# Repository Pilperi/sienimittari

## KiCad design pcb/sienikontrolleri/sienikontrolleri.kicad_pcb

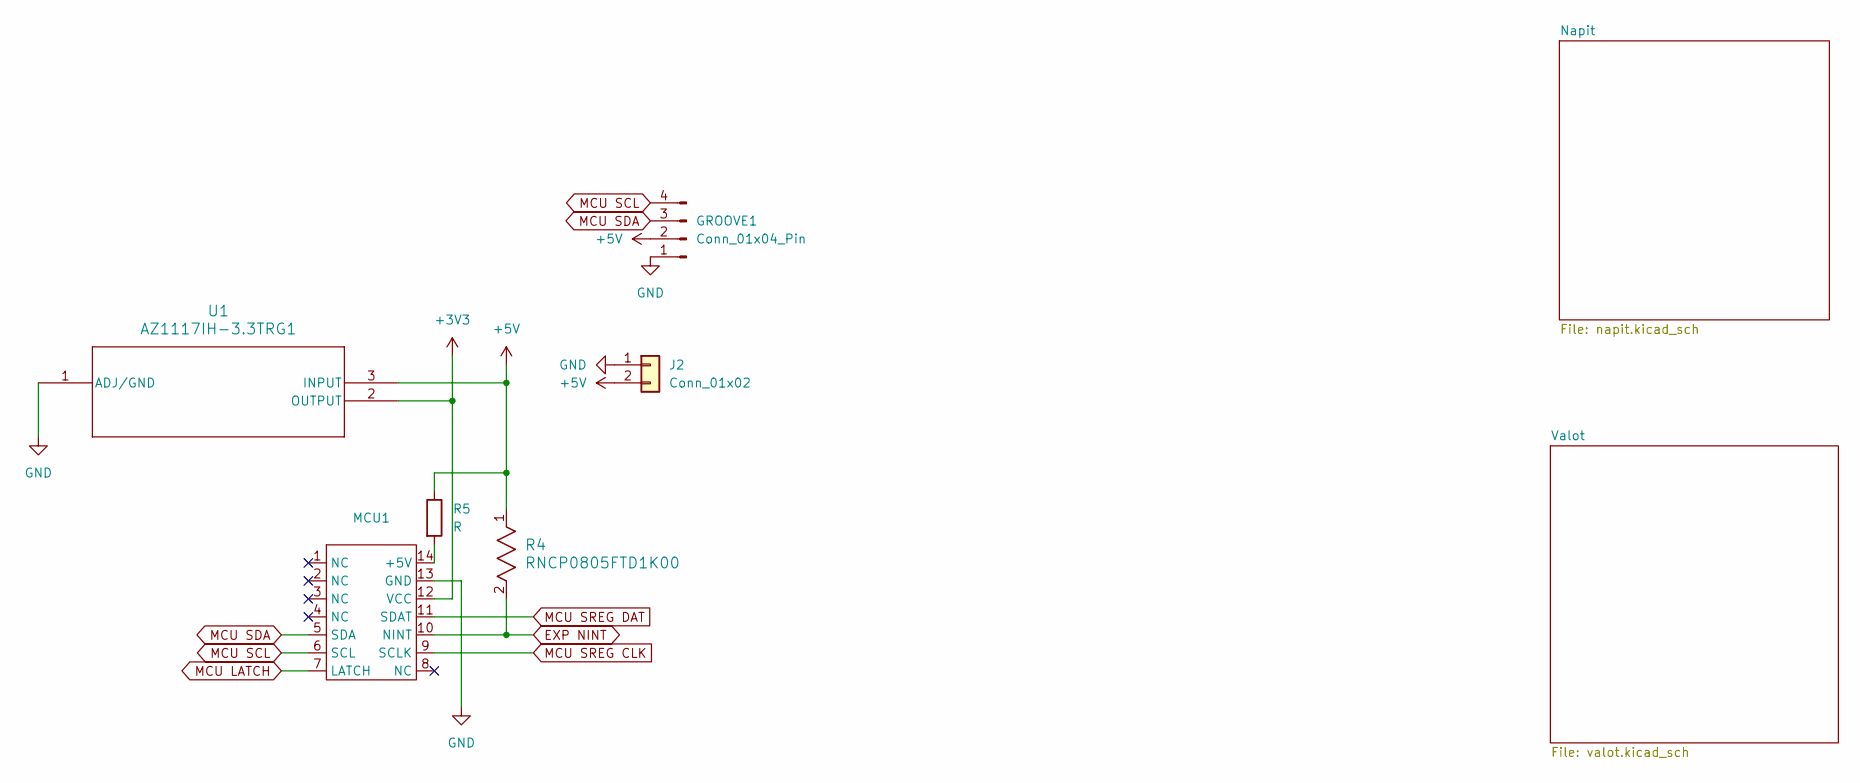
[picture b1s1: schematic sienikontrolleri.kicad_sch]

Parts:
GROOVE1: Conn_01x04_Pin; PinHeader_1x04_P2.00mm_Vertical
J2: Conn_01x02; PinHeader_1x02_P2.54mm_Vertical
MCU1: MCU 14
R4: RNCP0805FTD1K00; STA_RNCP0805_STP
R5: R; R_0805_2012Metric_Pad1.20x1.40mm_HandSolder
U1: AZ1117IH-3.3TRG1; SOT223_AZ1117I_6P5X3P5_DIO

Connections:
+3V3: MCU1.12 (VCC), U1.2 (OUTPUT)
+5V: GROOVE1.2, J2.2, R4.1, R5.1, U1.3 (INPUT); also elsewhere on the board
EXP NINT: MCU1.10 (NINT), R4.2; also elsewhere on the board
GND: GROOVE1.1, J2.1, MCU1.13 (GND), U1.1 (ADJ/GND); also elsewhere on the board
MCU LATCH: MCU1.7 (LATCH); also elsewhere on the board
MCU SCL: GROOVE1.4, MCU1.6 (SCL); also elsewhere on the board
MCU SDA: GROOVE1.3, MCU1.5 (SDA); also elsewhere on the board
MCU SREG CLK: MCU1.9 (SCLK); also elsewhere on the board
MCU SREG DAT: MCU1.11 (SDAT); also elsewhere on the board
unnamed: MCU1.14 (+5V), R5.2

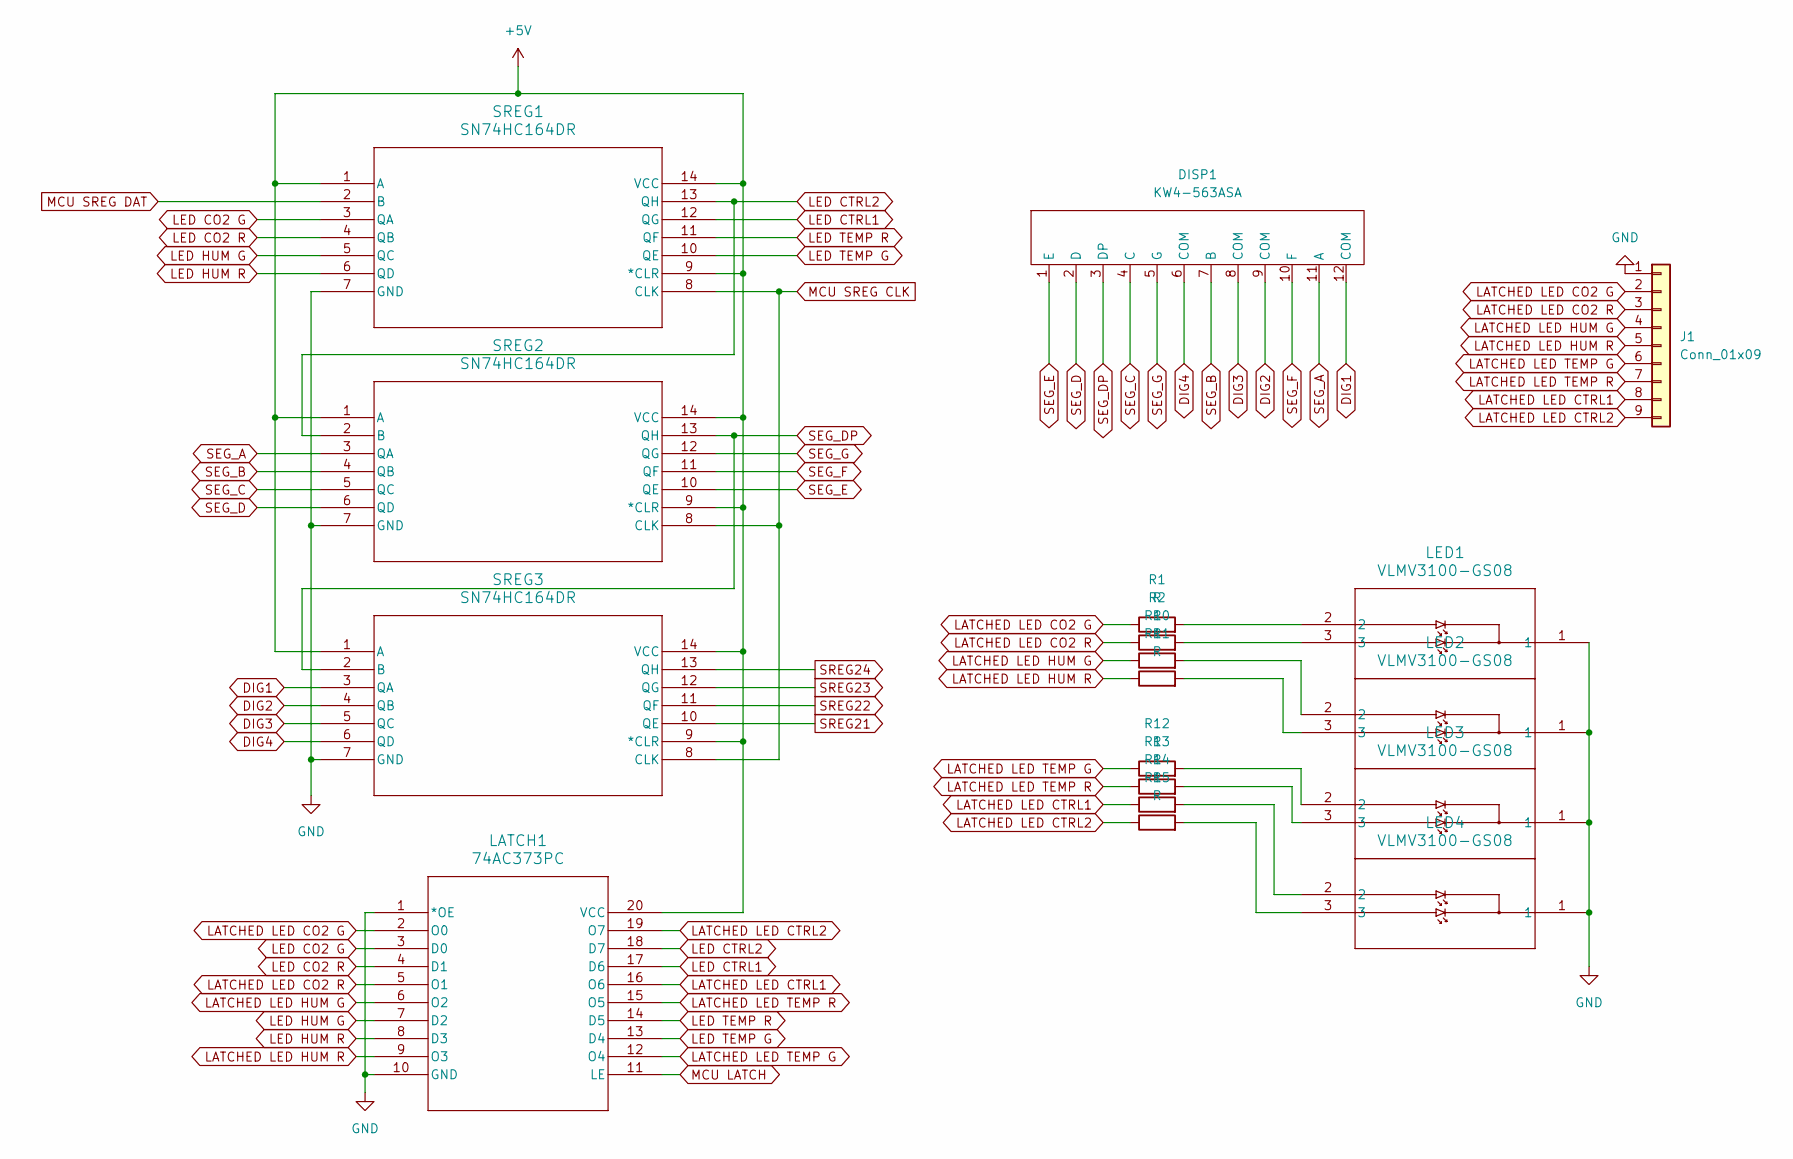
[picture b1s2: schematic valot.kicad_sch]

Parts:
DISP1: KW4-563ASA
J1: Conn_01x09; PinHeader_1x09_P2.54mm_Vertical
LATCH1: 74AC373PC; PDIP20_26P42X6P6_ONS
LED1, LED2, LED3, LED4: VLMV3100-GS08; VLMV3100_VIS
R1, R2, R10, R11, R12, R13, R14, R15: R; R_0805_2012Metric_Pad1.20x1.40mm_HandSolder
SREG1, SREG2, SREG3: SN74HC164DR; D14

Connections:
+5V: LATCH1.20 (VCC), SREG1.1 (A), SREG1.9 (*CLR), SREG1.14 (VCC), SREG2.1 (A), SREG2.9 (*CLR), SREG2.14 (VCC), SREG3.1 (A), SREG3.9 (*CLR), SREG3.14 (VCC); also elsewhere on the board
DIG1: DISP1.12 (COM), SREG3.3 (QA)
DIG2: DISP1.9 (COM), SREG3.4 (QB)
DIG3: DISP1.8 (COM), SREG3.5 (QC)
DIG4: DISP1.6 (COM), SREG3.6 (QD)
GND: J1.1, LATCH1.1 (*OE), LATCH1.10 (GND), LED1.1, LED2.1, LED3.1, LED4.1, SREG1.7 (GND), SREG2.7 (GND), SREG3.7 (GND); also elsewhere on the board
LATCHED LED CO2 G: J1.2, LATCH1.2 (O0), R1.1
LATCHED LED CO2 R: J1.3, LATCH1.5 (O1), R2.1
LATCHED LED CTRL1: J1.8, LATCH1.16 (O6), R14.1
LATCHED LED CTRL2: J1.9, LATCH1.19 (O7), R15.1
LATCHED LED HUM G: J1.4, LATCH1.6 (O2), R10.1
LATCHED LED HUM R: J1.5, LATCH1.9 (O3), R11.1
LATCHED LED TEMP G: J1.6, LATCH1.12 (O4), R12.1
LATCHED LED TEMP R: J1.7, LATCH1.15 (O5), R13.1
LED CO2 G: LATCH1.3 (D0), SREG1.3 (QA)
LED CO2 R: LATCH1.4 (D1), SREG1.4 (QB)
LED CTRL1: LATCH1.17 (D6), SREG1.12 (QG)
LED CTRL2: LATCH1.18 (D7), SREG1.13 (QH), SREG2.2 (B)
LED HUM G: LATCH1.7 (D2), SREG1.5 (QC)
LED HUM R: LATCH1.8 (D3), SREG1.6 (QD)
LED TEMP G: LATCH1.13 (D4), SREG1.10 (QE)
LED TEMP R: LATCH1.14 (D5), SREG1.11 (QF)
MCU LATCH: LATCH1.11 (LE); also elsewhere on the board
MCU SREG CLK: SREG1.8 (CLK), SREG2.8 (CLK), SREG3.8 (CLK); also elsewhere on the board
MCU SREG DAT: SREG1.2 (B); also elsewhere on the board
unnamed: LED1.2, R1.2
unnamed: LED1.3, R2.2
unnamed: LED2.2, R10.2
unnamed: LED2.3, R11.2
unnamed: LED3.2, R12.2
unnamed: LED3.3, R13.2
unnamed: LED4.2, R14.2
unnamed: LED4.3, R15.2
SEG_A: DISP1.11 (A), SREG2.3 (QA)
SEG_B: DISP1.7 (B), SREG2.4 (QB)
SEG_C: DISP1.4 (C), SREG2.5 (QC)
SEG_D: DISP1.2 (D), SREG2.6 (QD)
SEG_DP: DISP1.3 (DP), SREG2.13 (QH), SREG3.2 (B)
SEG_E: DISP1.1 (E), SREG2.10 (QE)
SEG_F: DISP1.10 (F), SREG2.11 (QF)
SEG_G: DISP1.5 (G), SREG2.12 (QG)
SREG21: SREG3.10 (QE)
SREG22: SREG3.11 (QF)
SREG23: SREG3.12 (QG)
SREG24: SREG3.13 (QH)

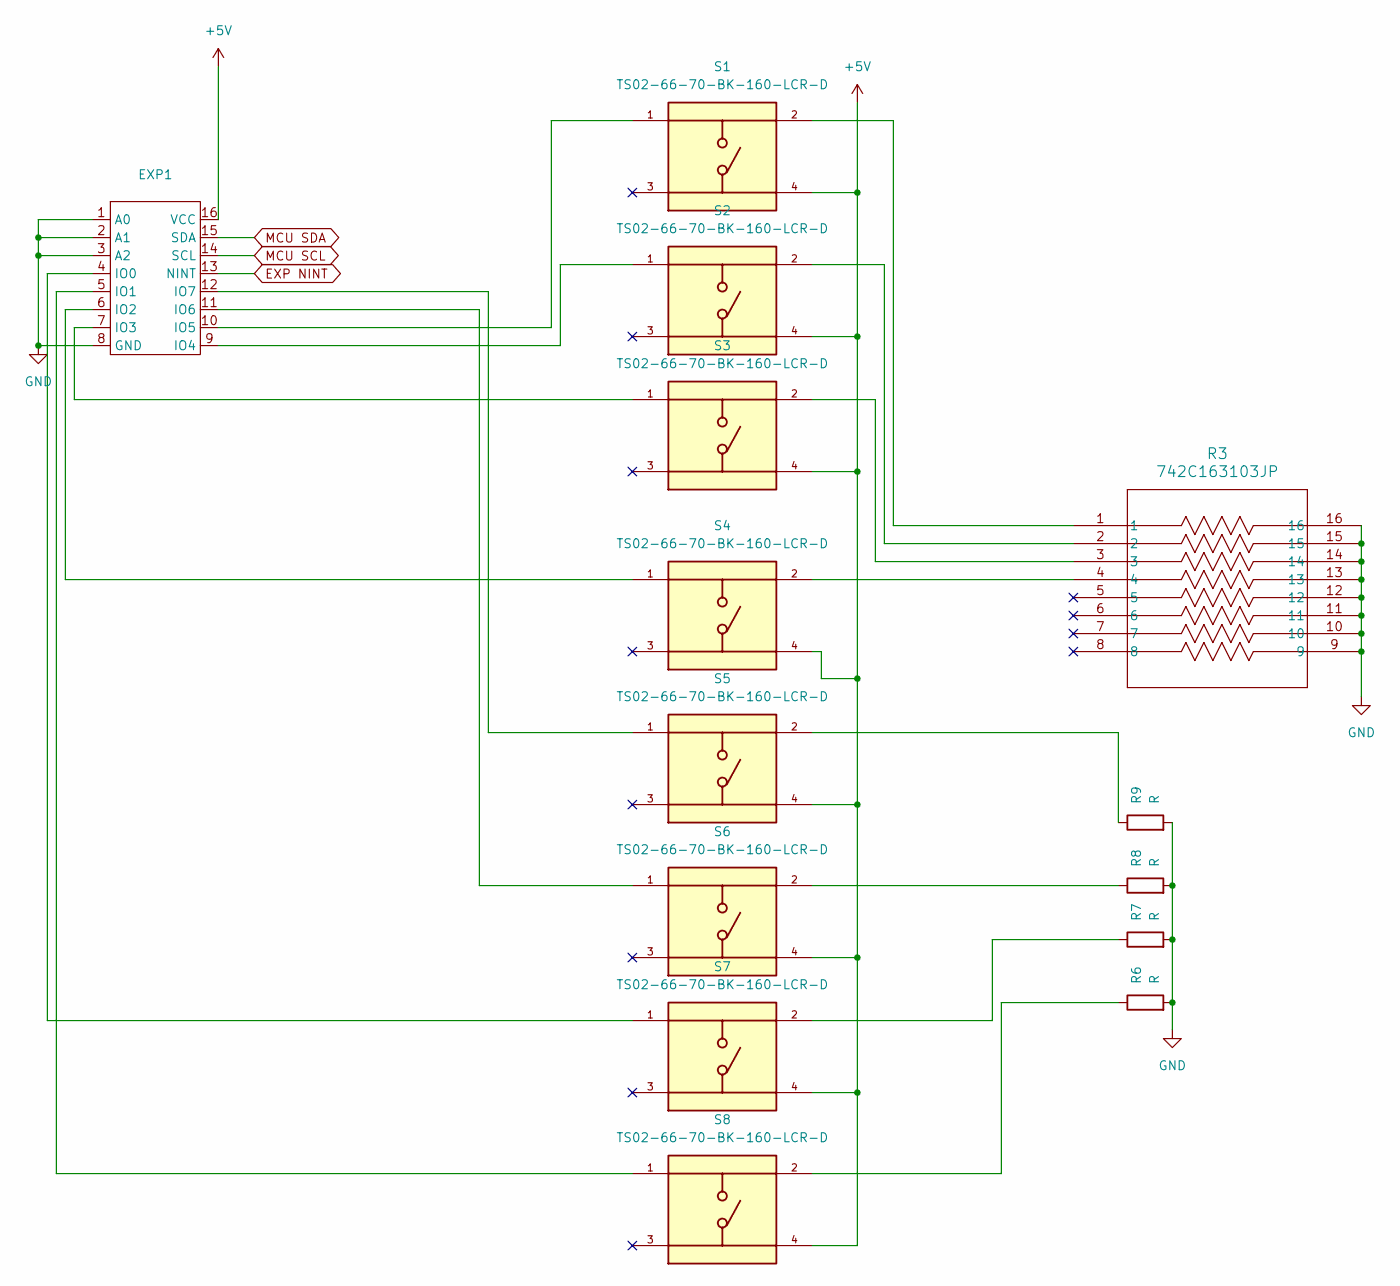
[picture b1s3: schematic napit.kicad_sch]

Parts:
EXP1: TSSOP-16_4.4x5mm_P0.65mm
R3: 742C163103JP; RES_CTS74X_6P4X1P6_CTS
R6, R7, R8, R9: R; R_0805_2012Metric_Pad1.20x1.40mm_HandSolder
S1, S2, S3, S4, S5, S6, S7, S8: TS02-66-70-BK-160-LCR-D; SW_TS02-66-70-BK-160-LCR-D; PARTREV 1.0

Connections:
+5V: EXP1.16 (VCC), S1.4, S2.4, S3.4, S4.4, S5.4, S6.4, S7.4, S8.4; also elsewhere on the board
EXP NINT: EXP1.13 (NINT); also elsewhere on the board
GND: EXP1.1 (A0), EXP1.2 (A1), EXP1.3 (A2), EXP1.8 (GND), R3.9, R3.10, R3.11, R3.12, R3.13, R3.14, R3.15, R3.16, R6.2, R7.2, R8.2, R9.2; also elsewhere on the board
MCU SCL: EXP1.14 (SCL); also elsewhere on the board
MCU SDA: EXP1.15 (SDA); also elsewhere on the board
unnamed: EXP1.4 (IO0), S7.1
unnamed: EXP1.5 (IO1), S8.1
unnamed: EXP1.6 (IO2), S4.1
unnamed: EXP1.7 (IO3), S3.1
unnamed: EXP1.9 (IO4), S2.1
unnamed: EXP1.10 (IO5), S1.1
unnamed: EXP1.11 (IO6), S6.1
unnamed: EXP1.12 (IO7), S5.1
unnamed: R3.1, S1.2
unnamed: R3.2, S2.2
unnamed: R3.3, S3.2
unnamed: R3.4, S4.2
unnamed: R6.1, S8.2
unnamed: R7.1, S7.2
unnamed: R8.1, S6.2
unnamed: R9.1, S5.2

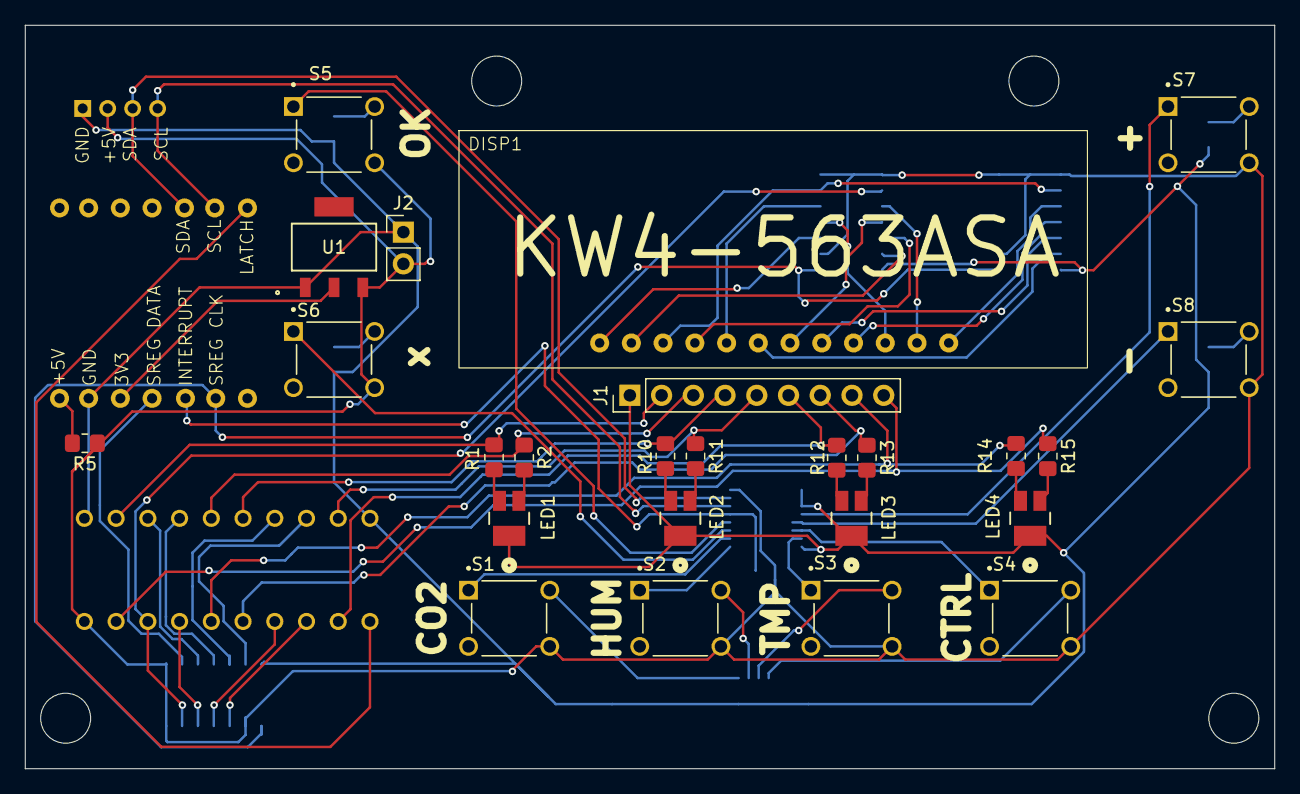
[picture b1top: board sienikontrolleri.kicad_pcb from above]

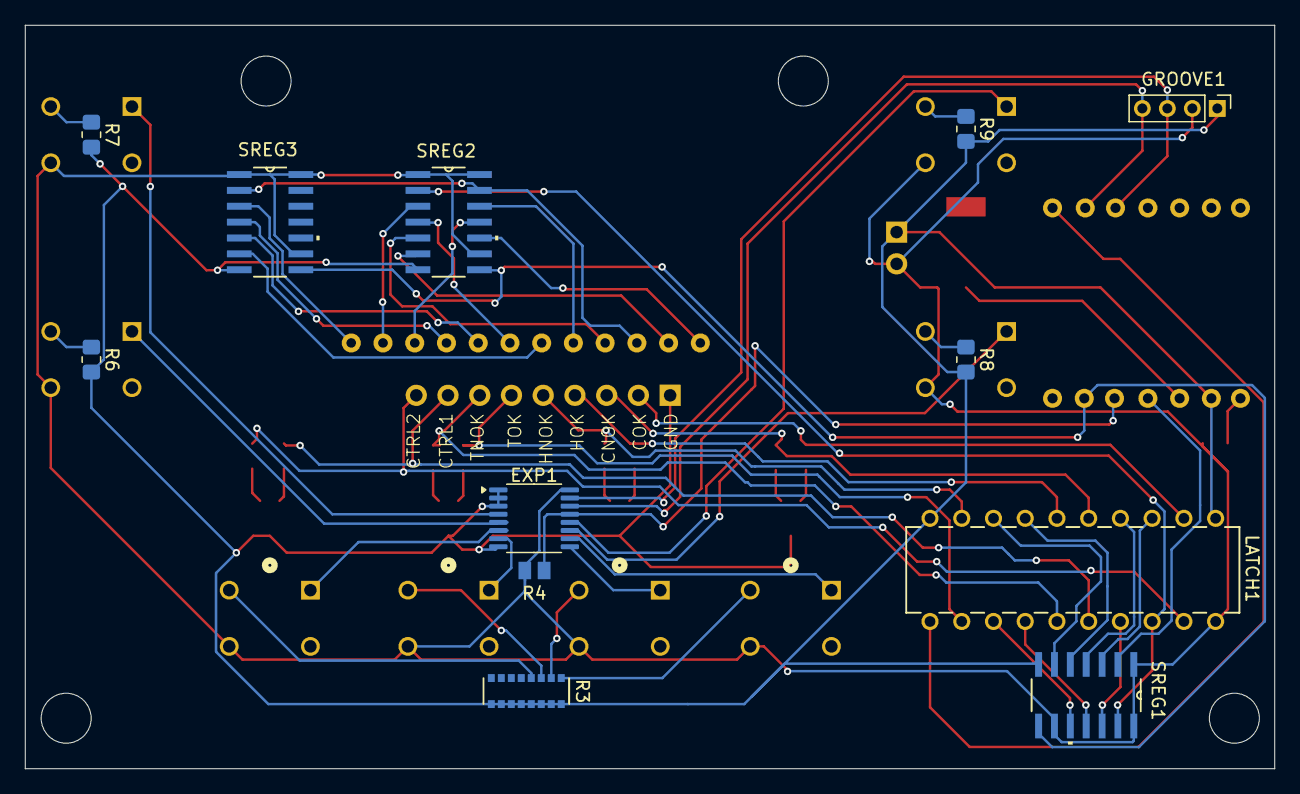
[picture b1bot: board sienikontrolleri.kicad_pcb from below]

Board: 2 copper layers, 100.0 x 59.5 mm, 38 parts (13 on the bottom side), 62 nets.

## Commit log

2024-11-02 Eka commit
2024-11-13 Muuta nimi ja korjaa viestintälogiikkaa. Rajamuokkaus oli killissä.
2024-11-15 Muokkaa UI-logiikkaa (ei vieläkään toimi)
2024-11-15 Lisää PCB
2024-11-23 Lisää rautatason yksikkötestit
2024-11-23 Tuunaa koodi vastaamaan tilattua PCB:tä (piuhoituksia tarvitsi muuttaa)
2024-11-23 Poista PCB-kansiosta kaikki turha
2024-11-23 Laita nappimääritykset vastaamaan PCB:tä
2024-11-23 Lisää ruuduntyhjäysfunktio
2024-11-23 Lisää PCB:n skeema-PDF
2024-11-23 Muokkaa nollan näyttöaikaa inhimillisemmäksi (vilkkui pahasti)
2025-07-14 Lisää loggeri ja sensoriton debug-moodi
2025-08-04 Toteuta rajojen muokkaaminen namiskojen avulla
2026-03-13 Kaikki paskaksi AVR-siirrosta varten. Numeronäyttö johonkin kondikseen.
2026-03-14 Lisätty gitignore... (mm)
2026-03-14 Parantele numeronäyttöä
2026-03-15 Käytä timer0 seitsensegmenttiin
2026-03-18 Siirry interrupt-pohjaiseen seitsensegmenttiin
2026-03-26 Ynnää I2C-väylän I/O-laajennin
